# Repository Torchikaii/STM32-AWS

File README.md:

Warning: Project is in very early develpment stage, so only maintainers know how to use it 😊.
Don't waste your time by trying to set things up, documentation is either outdated or AI generated or unclear.
It's now being presented as an idea, not as a project you should use. 

# STM32-AWS

CI/CD pipeline for STM32 projects with STM32CubeMX automation.

## Quick Start

See [docs/getting-started.md](docs/getting-started.md)

## What This Does

- Generates STM32 code from CubeMX .ioc files
- Compiles with ARM GCC
- Flashes to STM32F439 MCU

## Documentation

- [Getting Started](docs/getting-started.md)
- [Testing Locally](docs/testing-CICD-locally.md)

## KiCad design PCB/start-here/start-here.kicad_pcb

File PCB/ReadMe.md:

Schematics file is in: PCB_Project -> Sheet1.SchDoc

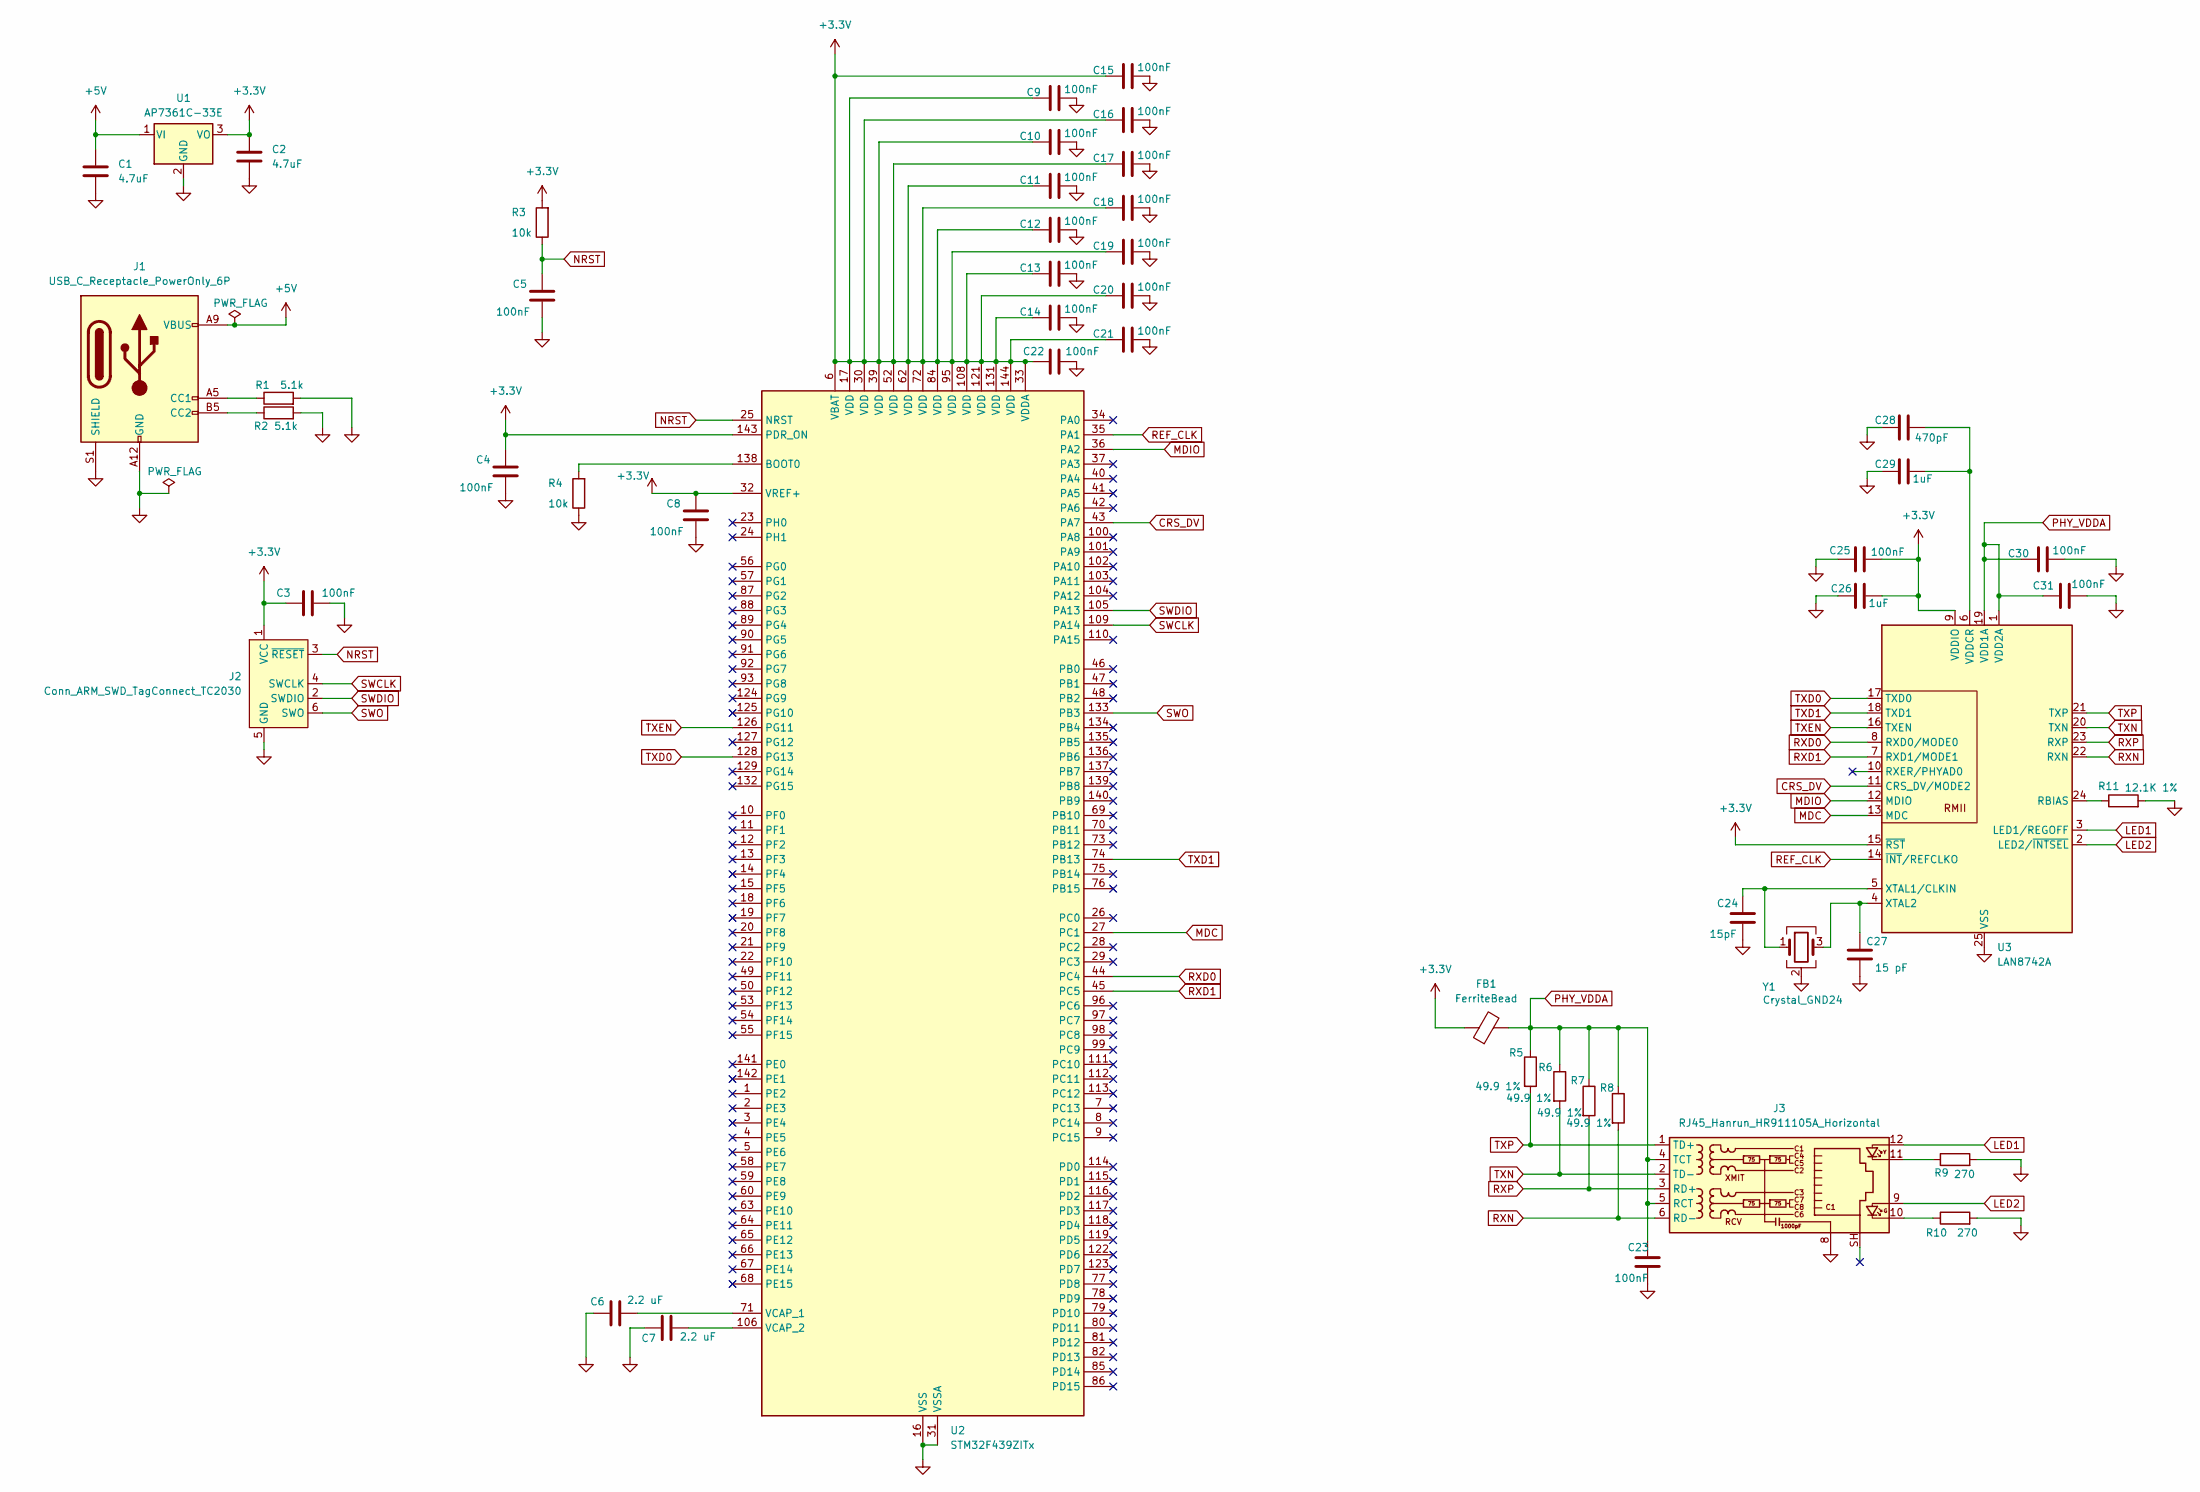
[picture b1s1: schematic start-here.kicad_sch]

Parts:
C1, C2: 4.7uF; C_0603_1608Metric
C3, C4, C5, C8, C9, C10, C11, C12, C13, C14, C15, C16, C17, C18, C19, C20, C21, C22, C23, C25, C30, C31: 100nF; C_0603_1608Metric
C6, C7: 2.2 uF; C_0603_1608Metric
C24: 15pF; C_0603_1608Metric
C26, C29: 1uF; C_0603_1608Metric
C27: 15 pF; C_0603_1608Metric
C28: 470pF; C_0603_1608Metric
FB1: FerriteBead; R_0603_1608Metric
J1: USB_C_Receptacle_PowerOnly_6P; USB_C_Receptacle_GCT_USB4125-xx-x-0190_6P_TopMnt_Horizontal
J2: Conn_ARM_SWD_TagConnect_TC2030; Tag-Connect_TC2030-IDC-FP_2x03_P1.27mm_Vertical
J3: RJ45_Hanrun_HR911105A_Horizontal
R1, R2: 5.1k; R_0603_1608Metric
R3, R4: 10k; R_0603_1608Metric
R5, R6, R7, R8: 49.9 1%; R_0603_1608Metric
R9, R10: 270; R_0603_1608Metric
R11: 12.1K 1%; R_0603_1608Metric
U1: AP7361C-33E; SOT-223-3_TabPin2
U2: STM32F439ZITx; LQFP-144_20x20mm_P0.5mm
U3: LAN8742A; VQFN-24-1EP_4x4mm_P0.5mm_EP2.5x2.5mm_ThermalVias
Y1: Crystal_GND24; Crystal_SMD_3225-4Pin_3.2x2.5mm

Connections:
+3.3V: C2.1, C3.2, C4.2, C8.2, C9.1, C10.1, C11.1, C12.1, C13.1, C14.1, C15.1, C16.1, C17.1, C18.1, C19.1, C20.1, C21.1, C22.2, C25.2, C26.2, FB1.1, J2.1 (VCC), R3.2, U1.3 (VO), U2.6 (VBAT), U2.17 (VDD), U2.30 (VDD), U2.32 (VREF+), U2.33 (VDDA), U2.39 (VDD), U2.52 (VDD), U2.62 (VDD), U2.72 (VDD), U2.84 (VDD), U2.95 (VDD), U2.108 (VDD), U2.121 (VDD), U2.131 (VDD), U2.143 (PDR_ON), U2.144 (VDD), U3.9 (VDDIO), U3.15 (~RST)
+5V: C1.1, J1.A9 (VBUS), J1.B9 (VBUS), U1.1 (VI)
CRS_DV: U2.43 (PA7), U3.11 (CRS_DV/MODE2)
GND: C1.2, C2.2, C3.1, C4.1, C5.1, C6.1, C7.1, C8.1, C9.2, C10.2, C11.2, C12.2, C13.2, C14.2, C15.2, C16.2, C17.2, C18.2, C19.2, C20.2, C21.2, C22.1, C23.2, C24.2, C25.1, C26.1, C27.2, C28.1, C29.1, C30.2, C31.2, J1.A12 (GND), J1.B12 (GND), J1.S1 (SHIELD), J2.5 (GND), J3.8, R1.2, R2.2, R4.1, R9.2, R10.2, R11.2, U1.2 (GND), U2.16 (VSS), U2.31 (VSSA), U2.38 (VSS), U2.51 (VSS), U2.61 (VSS), U2.83 (VSS), U2.94 (VSS), U2.107 (VSS), U2.120 (VSS), U2.130 (VSS), U3.25 (VSS), Y1.2 (G), Y1.4 (G)
LED1: J3.12, U3.3 (LED1/REGOFF)
LED2: J3.9, U3.2 (LED2/~INTSEL)
MDC: U2.27 (PC1), U3.13 (MDC)
MDIO: U2.36 (PA2), U3.12 (MDIO)
NRST: C5.2, J2.3 (~RESET), R3.1, U2.25 (NRST)
unnamed: J1.A5 (CC1), R1.1
unnamed: J1.B5 (CC2), R2.1
unnamed: J3.10, R10.1
unnamed: J3.11, R9.1
unnamed: R4.2, U2.138 (BOOT0)
unnamed: C6.2, U2.71 (VCAP_1)
unnamed: C7.2, U2.106 (VCAP_2)
unnamed: R11.1, U3.24 (RBIAS)
unnamed: C28.2, C29.2, U3.6 (VDDCR)
unnamed: C24.1, U3.5 (XTAL1/CLKIN), Y1.1
unnamed: C27.1, U3.4 (XTAL2), Y1.3
PHY_VDDA: C23.1, C30.1, C31.1, FB1.2, J3.4 (TCT), J3.5 (RCT), R5.1, R6.1, R7.1, R8.1, U3.1 (VDD2A), U3.19 (VDD1A)
REF_CLK: U2.35 (PA1), U3.14 (~INT/REFCLKO)
RXD0: U2.44 (PC4), U3.8 (RXD0/MODE0)
RXD1: U2.45 (PC5), U3.7 (RXD1/MODE1)
RXN: J3.6 (RD-), R8.2, U3.22 (RXN)
RXP: J3.3 (RD+), R7.2, U3.23 (RXP)
SWCLK: J2.4 (SWCLK), U2.109 (PA14)
SWDIO: J2.2 (SWDIO), U2.105 (PA13)
SWO: J2.6 (SWO), U2.133 (PB3)
TXD0: U2.128 (PG13), U3.17 (TXD0)
TXD1: U2.74 (PB13), U3.18 (TXD1)
TXEN: U2.126 (PG11), U3.16 (TXEN)
TXN: J3.2 (TD-), R6.2, U3.20 (TXN)
TXP: J3.1 (TD+), R5.2, U3.21 (TXP)

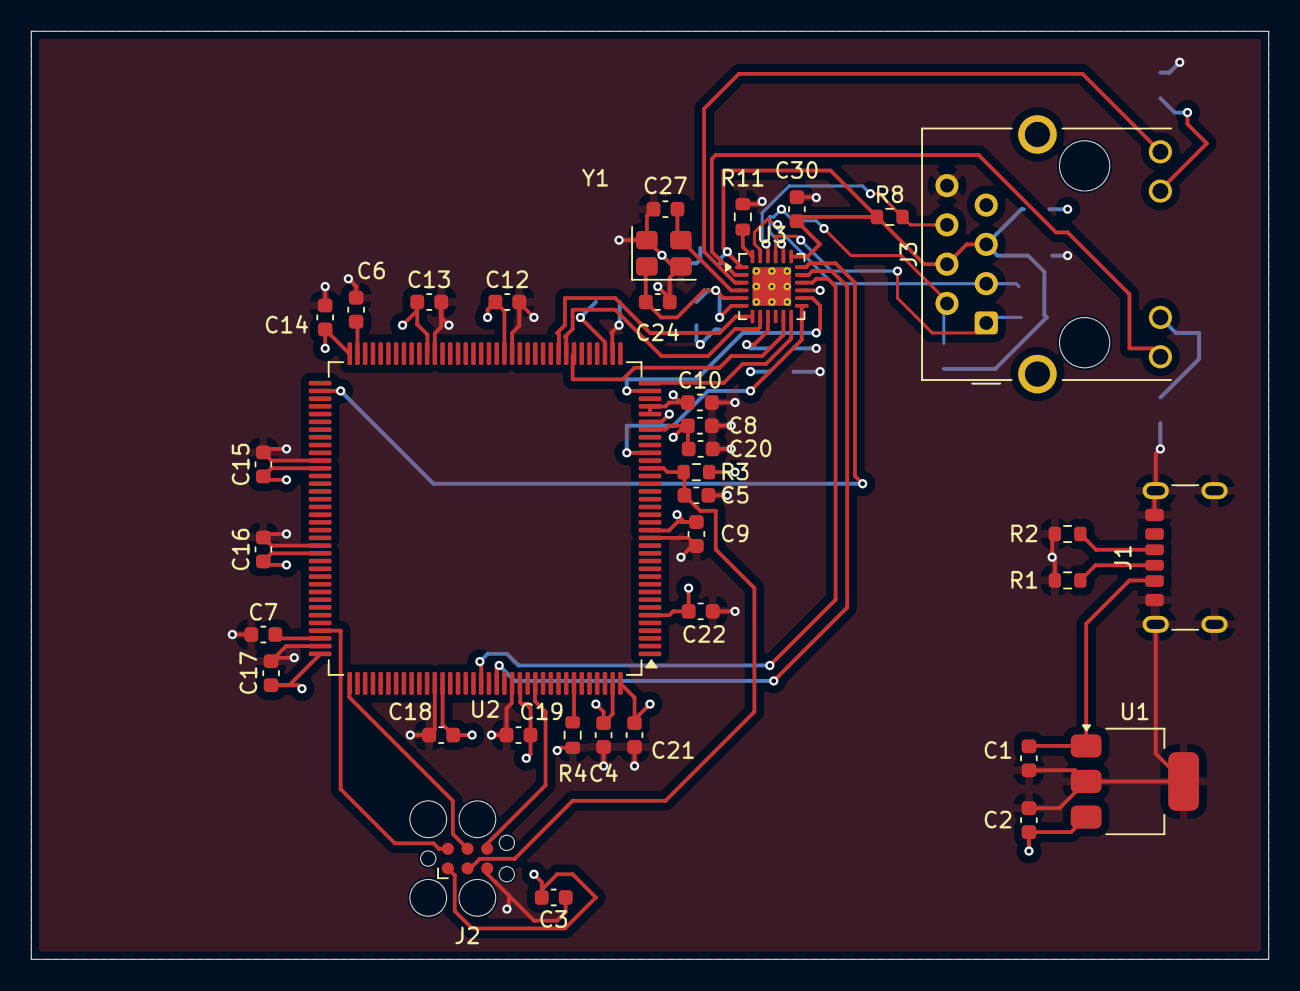
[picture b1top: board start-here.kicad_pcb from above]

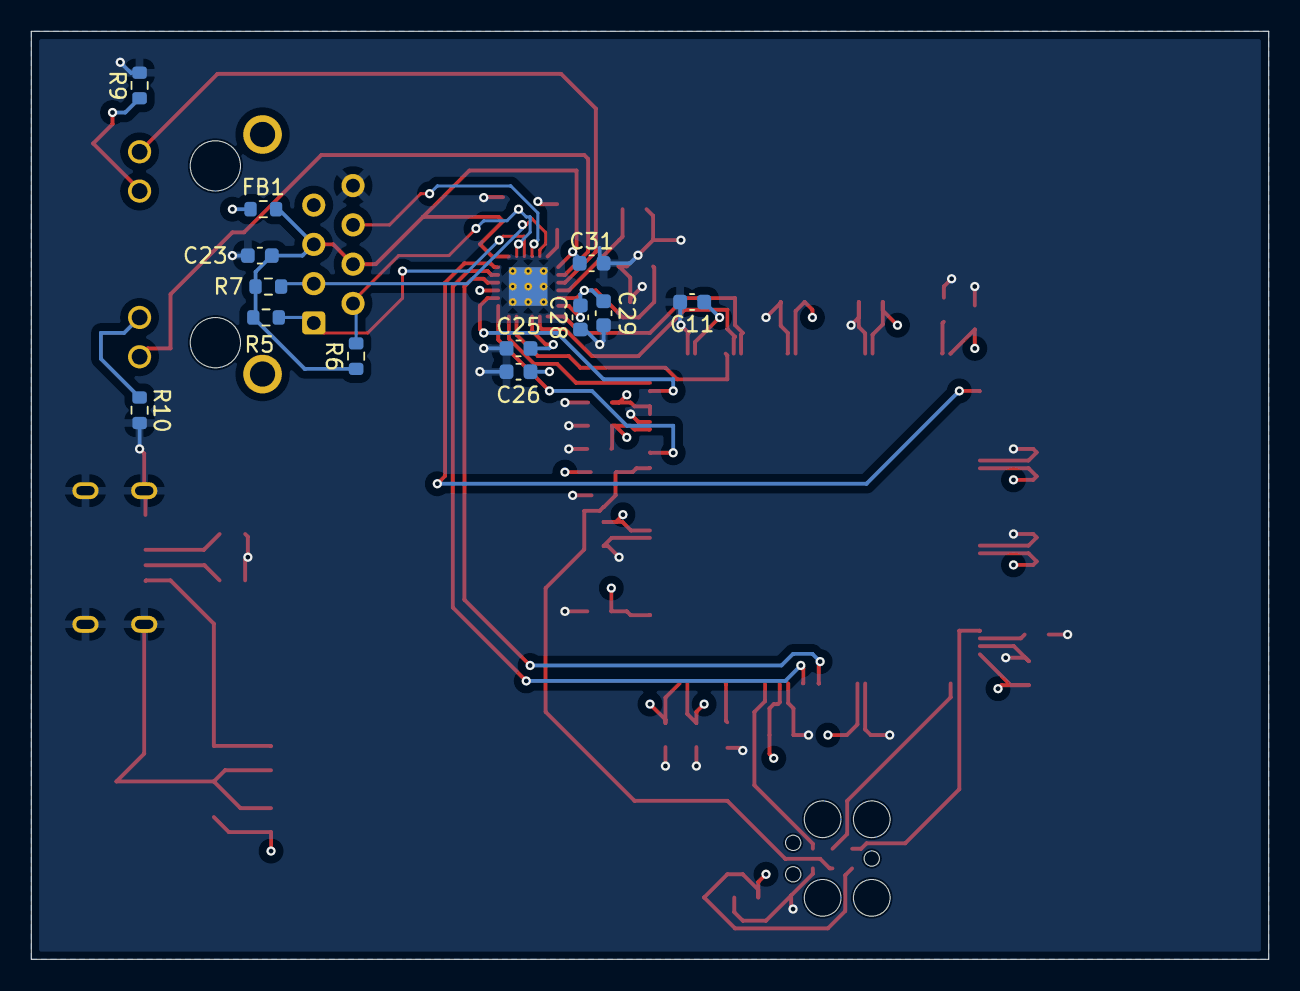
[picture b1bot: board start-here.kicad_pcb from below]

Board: 4 copper layers, 80.0 x 60.0 mm, 50 parts (13 on the bottom side), 34 nets.

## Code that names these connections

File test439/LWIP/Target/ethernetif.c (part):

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    __HAL_RCC_GPIOB_CLK_ENABLE();
    __HAL_RCC_GPIOG_CLK_ENABLE();
    /**ETH GPIO Configuration
    PC1     ------> ETH_MDC
    PA1     ------> ETH_REF_CLK
    PA2     ------> ETH_MDIO
    PA7     ------> ETH_CRS_DV
    PC4     ------> ETH_RXD0
    PC5     ------> ETH_RXD1
    PB13     ------> ETH_TXD1
    PG11     ------> ETH_TX_EN
    PG13     ------> ETH_TXD0
    */
    GPIO_InitStruct.Pin = GPIO_PIN_1|GPIO_PIN_4|GPIO_PIN_5;
    GPIO_InitStruct.Mode = GPIO_MODE_AF_PP;
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    __HAL_RCC_ETH_CLK_DISABLE();

    /**ETH GPIO Configuration
    PC1     ------> ETH_MDC
    PA1     ------> ETH_REF_CLK
    PA2     ------> ETH_MDIO
    PA7     ------> ETH_CRS_DV
    PC4     ------> ETH_RXD0
    PC5     ------> ETH_RXD1
    PB13     ------> ETH_TXD1
    PG11     ------> ETH_TX_EN
    PG13     ------> ETH_TXD0
    */
    HAL_GPIO_DeInit(GPIOC, GPIO_PIN_1|GPIO_PIN_4|GPIO_PIN_5);

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                       PHI IO Functions
*******************************************************************************/
/**
  * @brief  Initializes the MDIO interface GPIO and clocks.
  * @param  None
  * @retval 0 if OK, -1 if ERROR
  */
int32_t ETH_PHY_IO_Init(void)
{
  /* We assume that MDIO GPIO configuration is already done
     in the ETH_MspInit() else it should be done here
  */

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
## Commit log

2025-08-01 added FreeRTOS initial program with blinking blue LED
2025-08-01 adding initial plan
2025-08-01 initial PR
2025-08-12 some hardware explanation
2025-08-12 explained RTOS in md
2025-08-13 docker test
2025-08-13 Update Dockerfile
2025-08-13 Update Dockerfile to add stm32cubemx
2025-08-13 changed cubemx version to 6.15.0
2025-08-13 download cubeMX from S3 bucket
2025-08-13 fixed to output
2025-08-13 generate script workflow
2025-08-13 new workflow to use docker container
2025-08-13 added workflow manual trigger
2025-08-14 Ensure necessary directories exist before restoring CubeMX cache
2025-08-14 Update stm32_generate_code.yml to use github.workspace and improve cache handling
2025-08-14 Rename HOME environment variable to CUBEMX_HOME for clarity in stm32_generate_code.yml
2025-08-14 Refactor script generation in stm32_generate_code.yml to use relative paths
2025-08-14 Update stm32_generate_code.yml to improve environment variable handling and streamline cache restoration
2025-08-14 Update stm32_generate_code.yml to replace HOME variable with absolute paths for cache restoration
2025-08-14 Update stm32_generate_code.yml to set HOME variable to a specific directory and adjust script paths for improved clarity
2025-08-14 Remove HOME variable from environment in stm32_generate_code.yml for improved clarity
2025-08-14 Initial PR (#2)
    * initial PR
    * some hardware explanation
    * explained RTOS in md
    * docker test
    * Update Dockerfile
    * Update Dockerfile to add stm32cubemx
2025-08-14 updated timeout to 20 minutes
2025-08-15 add toolchain configuration for Makefile
2025-08-15 update GitHub Actions workflow to use checkout@v5 and add firmware build step
2025-08-15 update project configuration for STM32CubeIDE toolchain and adjust function list sorting
2025-08-15 add toolchain configuration for Makefile in code generation script
2025-08-15 update GitHub Actions workflow to generate and build firmware with STM32CubeMX
2025-08-15 fix: correct configuration file extension in code generation script
2025-08-15 update: increase timeout for STM32CubeMX script execution
2025-08-15 update: modify generate_script.txt creation for STM32 project configuration
2025-08-15 update: add environment variables for STM32CubeMX script login
2025-08-15 update: enhance Dockerfile and GitHub Actions for ARM toolchain installation
2025-08-15 update: change working directory for firmware build in GitHub Actions
2025-08-15 update: enhance STM32CubeMX workflow with error handling and conditional steps
2025-08-16 update: modify project settings for STM32CubeMX to enable under root generation
2025-08-16 update: clean up Dockerfile by removing installation files after setup
2025-08-16 update: add pull request trigger for main branch in build-image.yml
2025-08-16 update: upgrade actions/checkout and docker/build-push-action versions in build-image.yml
2025-08-16 update: modify build-image.yml triggers and change STM32CubeMX runner image to dev
2025-08-16 update: adjust paths for firmware artifacts in stm32_generate_code.yml
2025-08-16 update: refine error handling and add debugging output in stm32_generate_code.yml
2025-08-16 update: streamline STM32CubeMX installation process in Dockerfile
2025-08-16 update: add build artifact verification and size enforcement in stm32_generate_code.yml
2025-08-16 update: enhance size budget enforcement and improve error handling in stm32_generate_code.yml
2025-08-16 update: specify working directory for size budget enforcement in stm32_generate_code.yml
2025-08-16 update: modify Reset_Handler check to exit gracefully in stm32_generate_code.yml
2025-08-16 update GitHub Actions workflow to use checkout@v5 and add firmware build step (#7)
    * update GitHub Actions workflow to use checkout@v5 and add firmware build step
    * update project configuration for STM32CubeIDE toolchain and adjust function list sorting
    * add toolchain configuration for Makefile in code generation script
    * update GitHub Actions workflow to generate and build firmware with STM32CubeMX
    * fix: correct configuration file extension in code generation script
    * update: increase timeout for STM32CubeMX script execution
2025-08-19 split datasheets
2025-08-19 intial test
2025-08-20 create .sh files
2025-08-21 send to wsl2
2025-08-21 github secrets to -> env variables
2025-08-21 adjusted workspace paths
2025-08-21 .gitattributes and continue even when failed
2025-08-21 debug output
2025-09-18 created gitleaks.yml file
2025-09-18 attempt to fix gitleaks.yml
2025-09-18 2nd attempt to fix gitleaks.yml
2025-09-18 3rd attempt to fix gitleaks.yml
2025-10-01 Updated README.md to indicate early development stage
2025-10-01 Added README.md
    Added text to README.md
2025-10-21 generated binary files from CubeIDE
2025-10-23 Added PCB folder and schematics
2025-10-23 Updated ReadMe file
2025-10-23 Removed Instrukijos.txt from the PCB folder
2025-10-23 Does't let to just change tu capital letter
2025-10-23 Changed to all capitals
2025-10-28 Shematics fix, added new components
2025-10-31 Added 6 schematics, added 2 describtions, about schematics
2025-11-02 Added 3 pin header so st-link could be programed
2025-11-02 Deleted unwanted files wrote the description in README file
2025-11-03 Started to trace PCB
2025-11-03 fixed paths to be relative
2025-11-03 Added MCU_WL schematics
2025-11-03 WL island
2025-11-03 more or less placed correctly
2025-11-03 half trace done
2025-11-03 still tracing
2025-11-03 tracing seems to be done
2025-11-03 redefine board shape
2025-11-03 PCB completed
2025-11-03 added gerber files
2025-11-09 added NC drill and fixed prjpcb paths to relative
2025-11-09 renamed initial PCB files and added pick and place files
    some errors remain in BOM doc, because some (like 3) components does not have supplier, but I guess it's not a big deal
2025-11-13 fixed another hardcoded path
2025-11-13 added 5V to shematic and removed WL MCU
2025-11-14 refactoring progress
2025-11-14 Schematics fixed
2025-11-14 reanotated schematics and updated pcb
    ESP12F footprint is missing...
2025-11-15 PCB ready for tracing
    note some old intlib libraries belonging to other projects were deleted. This may not be a problem cause altium chaches them. However if something goes wrong, updated intlib library should be importe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
2025-11-16 component placement checkpoint1
2025-11-16 fixed GND net label
2025-11-16 routing checkpoint2
    also set up via size rules
2025-11-16 components correctly placed
2025-11-16 tracing checkpoint1
2025-11-16 added screw holes to PCB
2025-11-16 done tracing
2025-11-16 fixed errors, verified by Design rule check tool
2025-11-16 poured polygon on top and bottom layers
2025-11-16 Added Gerber, NC drill and Pick and Place files
2025-11-24 add README.md and update comments
    needs refactorisation
2025-11-30 update readme and workflow comments
2025-12-08 fix README.md file and workflow comments
2025-12-08 docs: improve CI/CD documentation and fix security issue
    - Fix markdown heading hierarchy (h6 to h4) and punctuation in workflows README
2025-12-09 initial project with no code yet
2025-12-09 added bliking blue LED
2025-12-09 use new project in CI/CD
2025-12-09 fix CI/CD failing
2025-12-09 fix CI/CD
2025-12-09 update .ioc
    Sonnet 4.5: Perfect! I found the issue! Look at these critical differences:
2026-01-14 added project structure in README.md
2026-02-28 remove files and add generate_script.sh
2026-02-28 add run-cubemx.sh
2026-02-28 add compile and flash script
    script is working locally
2026-02-28 fix generate_script.sh now working
2026-02-28 reset LEDs
2026-02-28 add insight for troubleshooting in output.md
2026-03-12 intial context engineering with PRD
2026-03-12 update PRD
2026-03-12 add AGENTS.md
2026-03-12 add first plan
2026-03-13 add /docs
2026-03-21 update documentation
2026-03-21 Remove /build folder from tracking
2026-03-23 partially works, no video passtrough or some other issues
2026-03-23 update docs
2026-03-23 update actions workflow
2026-03-23 update github actions workflow
2026-03-23 fix github ctions workflow
2026-03-23 Refactor project (#30)
    * remove files and add generate_script.sh
    * add
    * add run-cubemx.sh
    * add compile and flash script
    script is working locally
    * fix generate_script.sh now working
2026-03-23 Add warning about project status and documentation
    Added a warning about the project's early development stage and unclear documentation.
2026-03-24 update docker tag in CI/CD
2026-03-25 fix documentation to provide reproducible steps
2026-03-25 update docs one more time
2026-03-25 update CI/CD to use docker image
2026-03-26 Adjust project for better readability and reusability (#32)
    * update docker tag in CI/CD
    * update documentation
    * fix documentation to provide reproducible steps
    * update docs one more time
    * update CI/CD to use docker image
    * update documentation
2026-03-26 initial setup-repo.sh
2026-03-26 add auto install script
    paths may be adjusted as in /opt folder cubemx stopped finding .ioc file
2026-03-27 update cubemx to use symlink
2026-03-28 works partialy
2026-03-28 update docs with full local onboarding
2026-03-28 Update local installation (#34)
    * initial setup-repo.sh
    * add auto install script
    paths may be adjusted as in /opt folder cubemx stopped finding .ioc file
    * update cubemx to use symlink
    * works partialy
    * update docs with full local onboarding
2026-03-28 fix typo in docs
2026-03-30 update scripts
2026-03-30 simplified onboarding docs
    do not modify bash scripts inside the repo root after this commit inside this PR
2026-04-01 added plan for second phase
2026-04-01 update .gitignore to ignore swap files
2026-04-01 add LWIP middleware
2026-04-01 fix gitleaks false positive
2026-04-06 add network-connection.md to docs
2026-04-08 update documenation and recompile project
2026-04-15 ping is working
2026-04-17 initial context engineering plan executed
2026-05-04 progress
2026-05-04 initial plan
2026-05-04 further planning
2026-05-04 almost good
2026-05-06 add initial AWS docs
2026-05-06 update docs/
2026-05-08 update plans
2026-05-08 initial 4 phase plan
2026-05-08 update on mcu mocking
2026-05-08 add aws_iot_config.h
2026-05-08 compilation passed
2026-05-08 update docs/connecting-to-AWS.md
    in the docs tell to replace LwIP call in the while loop, because RTOS calls LwIP on it's own
2026-05-08 add coreMQTT
    added coremqtt submodule and new file core_mqtt_config.h
2026-05-08 save
2026-05-08 add python file for reading terminal messages
2026-05-20 this is more like a stash than commit
2026-05-22 remove obsolete files
2026-05-22 regenerate code, and remove LWIP init from while loop
2026-05-22 regenerate one more time
2026-05-22 reset ethernet in cubemx
2026-05-22 update opencode pakcages
2026-05-23 disable data cache
2026-05-25 add initial schematic files
2026-06-01 Route RMII and update datasheets.md
2026-06-03 update schematics
2026-06-04 update schematics: update power on the PHY, connect LEDs and add ferrite bead
2026-06-04 schematic done, but not verified
2026-06-11 schematic done, no footprints
2026-06-11 add footprints to components and fix ECR
2026-06-16 placed components
2026-06-16 routed PCB, DRC violations present
2026-06-17 resize PCB and pour polygons
2026-06-17 fix silkscreen overlapping
2026-06-17 add example PCB

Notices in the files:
test439/LWIP/Target/ethernetif.c:
Copyright (c) 2026 STMicroelectronics.
All rights reserved.
This software is licensed under terms that can be found in the LICENSE file
